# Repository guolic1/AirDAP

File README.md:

# AirDAP

基于 ESP32-S3 的无线调试器，支持 CMSIS-DAP 调试烧录和串口通信。
通过 USB 直连，或使用 Windows / Linux 主机服务将网络设备映射为 USB 调试器和串口。

支持蓝牙 / USB 配网、Wi-Fi 扫描、设备信息查看及 OTA 升级。

## 快速开始

从 [Releases](https://github.com/guolic1/AirDAP/releases/latest) 下载服务管理器和固件：

- **Windows**：双击服务管理器安装服务，可设置端口和开机自启。默认管理地址为 `http://airdap.localhost:8080`。
- **Linux**：按 [主机服务说明](host/README.md) 构建并安装 systemd 服务。
- **固件**：`app.bin` 用于 OTA；`full.bin` 用于首次烧录或恢复，写入地址为 `0x0`，会清除配网数据。

Windows 的 USB/IP 映射需安装 [usbip-win2 驱动和客户端](https://github.com/vadimgrn/usbip-win2/releases)。

## 项目目录

- [firmware/](firmware/README.md)：ESP-IDF 固件与构建说明。
- [host/](host/README.md)：Rust 主机服务、Web 管理页和服务安装工具。
- [circuit/](circuit/)：KiCad 原理图与 PCB。
- [docs/hardware-pinmap.md](docs/hardware-pinmap.md)：硬件引脚约定。

## 许可证

[MIT](LICENSE)。第三方依赖遵循各自的许可证。

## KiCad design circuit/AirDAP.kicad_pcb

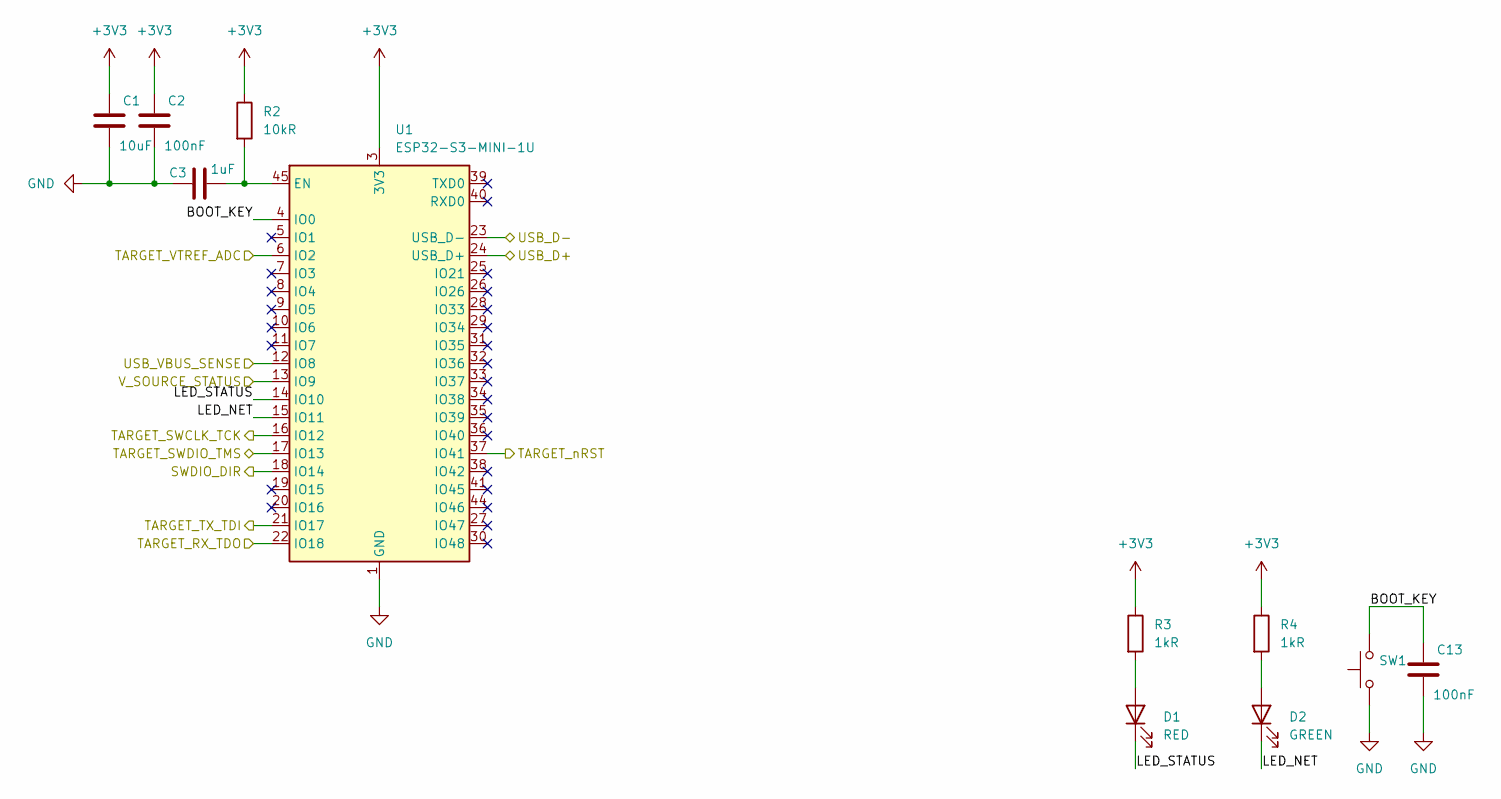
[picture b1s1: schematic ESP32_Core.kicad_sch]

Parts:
C1: 10uF; C_0402_1005Metric
C2, C13: 100nF; C_0402_1005Metric
C3: 1uF; C_0402_1005Metric
D1: RED; LED_0603_1608Metric
D2: GREEN; LED_0603_1608Metric
R2: 10kR; R_0402_1005Metric
R3, R4: 1kR; R_0402_1005Metric
SW1: SW_Push; SW_Push_SPST_NO_Alps_SKRK
U1: ESP32-S3-MINI-1U; ESP32-S2-MINI-1U

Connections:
+3V3: C1.1, C2.1, R2.1, R3.1, R4.1, U1.3 (3V3); also elsewhere on the board
/ESP32 Core/BOOT_KEY: C13.1, SW1.2, U1.4 (IO0)
/ESP32 Core/LED_NET: D2.1 (K), U1.15 (IO11)
/ESP32 Core/LED_STATUS: D1.1 (K), U1.14 (IO10)
/ESP32 Core/SWDIO_DIR: U1.18 (IO14); also elsewhere on the board
/ESP32 Core/TARGET_RX_TDO: U1.22 (IO18); also elsewhere on the board
/ESP32 Core/TARGET_SWCLK_TCK: U1.16 (IO12); also elsewhere on the board
/ESP32 Core/TARGET_SWDIO_TMS: U1.17 (IO13); also elsewhere on the board
/ESP32 Core/TARGET_TX_TDI: U1.21 (IO17); also elsewhere on the board
/ESP32 Core/TARGET_VTREF_ADC: U1.6 (IO2); also elsewhere on the board
/ESP32 Core/TARGET_nRST: U1.37 (IO41); also elsewhere on the board
/ESP32 Core/USB_D+: U1.24 (USB_D+); also elsewhere on the board
/ESP32 Core/USB_D-: U1.23 (USB_D-); also elsewhere on the board
/ESP32 Core/USB_VBUS_SENSE: U1.12 (IO8); also elsewhere on the board
/ESP32 Core/V_SOURCE_STATUS: U1.13 (IO9); also elsewhere on the board
GND: C1.2, C2.2, C3.1, C13.2, SW1.1, U1.1 (GND), U1.2 (GND), U1.42 (GND), U1.43 (GND), U1.46 (GND), U1.47 (GND), U1.48 (GND), U1.49 (GND), U1.50 (GND), U1.51 (GND), U1.52 (GND), U1.53 (GND), U1.54 (GND), U1.55 (GND), U1.56 (GND), U1.57 (GND), U1.58 (GND), U1.59 (GND), U1.60 (GND), U1.61 (GND), U1.62 (GND), U1.63 (GND), U1.64 (GND), U1.65 (GND); also elsewhere on the board
unnamed: D1.2 (A), R3.2
unnamed: D2.2 (A), R4.2
unnamed: C3.2, R2.2, U1.45 (EN)

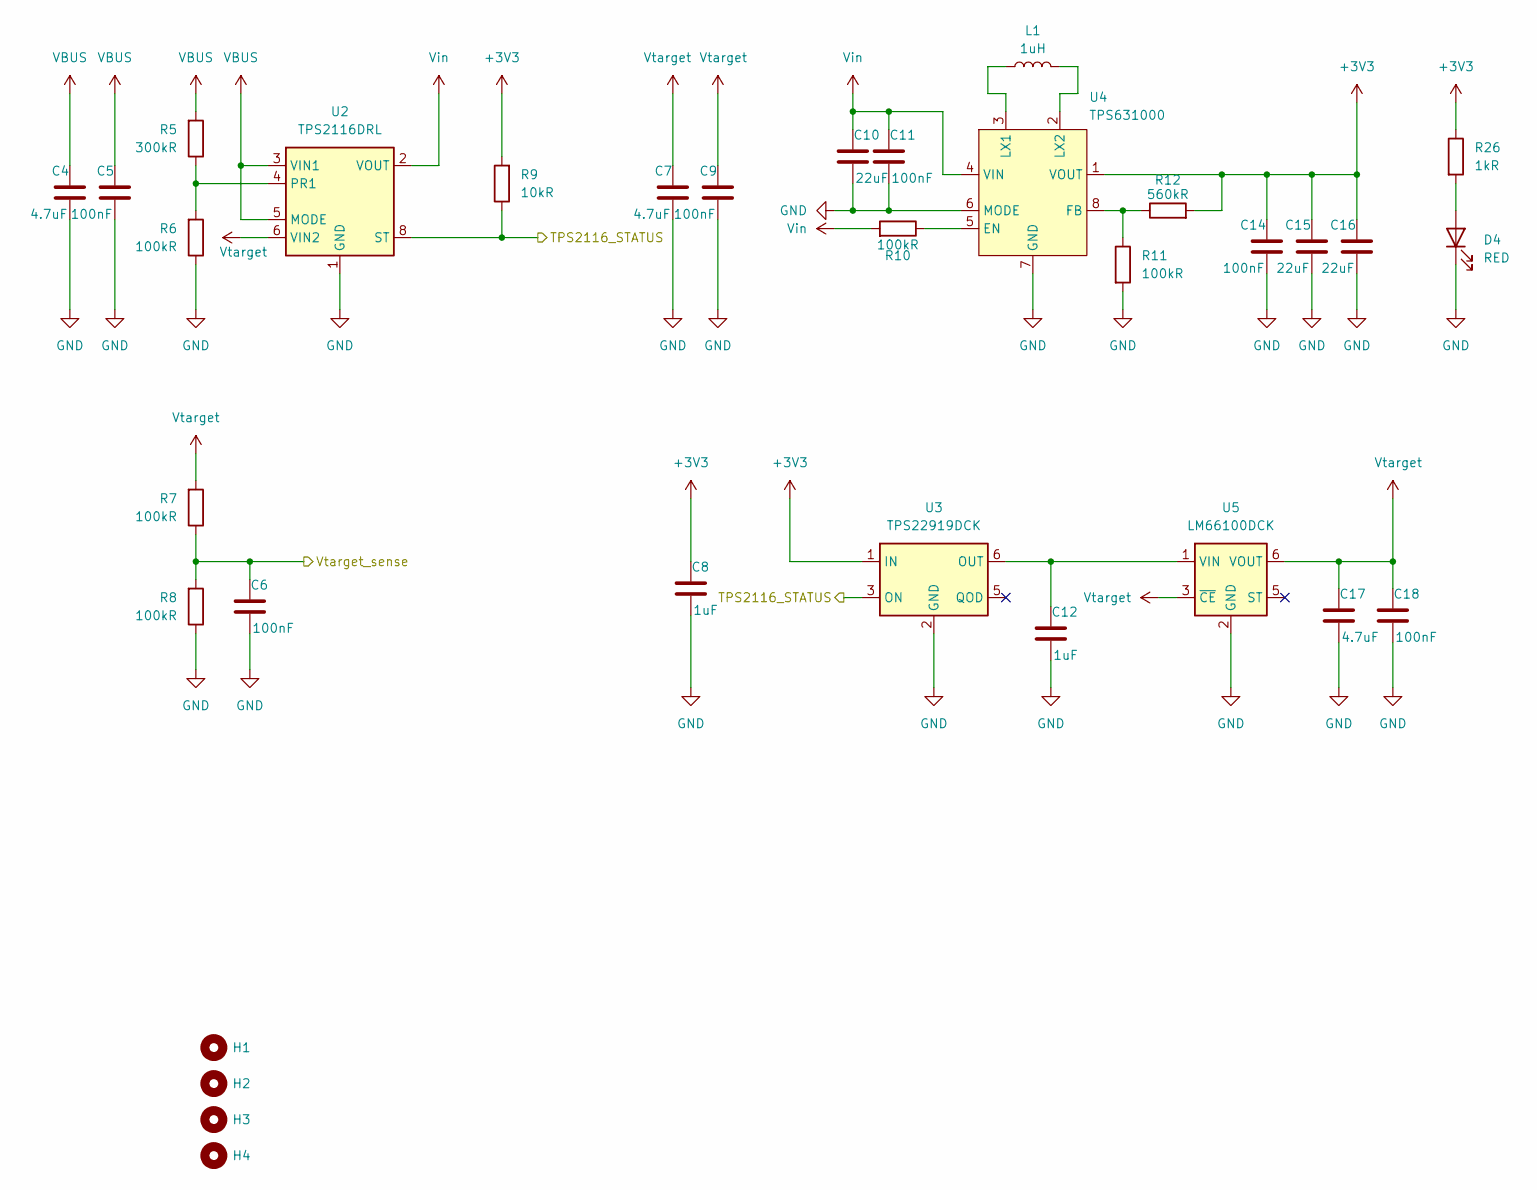
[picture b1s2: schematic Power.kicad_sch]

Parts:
C4, C7, C17: 4.7uF; C_0402_1005Metric
C5, C6, C9, C11, C14, C18: 100nF; C_0402_1005Metric
C8, C12: 1uF; C_0402_1005Metric
C10, C15, C16: 22uF; C_0603_1608Metric
D4: RED; LED_0603_1608Metric
H1, H2, H3, H4: MountingHole; MountingHole_2.2mm_M2
L1: 1uH; L_1008_2520Metric
R5: 300kR; R_0402_1005Metric
R6, R7, R8, R10, R11: 100kR; R_0402_1005Metric
R9: 10kR; R_0402_1005Metric
R12: 560kR; R_0402_1005Metric
R26: 1kR; R_0402_1005Metric
U2: TPS2116DRL; SOT-583-8
U3: TPS22919DCK; SOT-363_SC-70-6
U4: TPS631000; SOT-583-8
U5: LM66100DCK; SOT-363_SC-70-6

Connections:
+3V3: C8.1, C14.1, C15.1, C16.1, R9.2, R12.2, R26.1, U3.1 (IN), U4.1 (VOUT); also elsewhere on the board
/ESP32 Core/TARGET_VTREF_ADC: C6.1, R7.1, R8.2; also elsewhere on the board
/ESP32 Core/V_SOURCE_STATUS: R9.1, U2.8 (ST), U3.3 (ON); also elsewhere on the board
GND: C4.2, C5.2, C6.2, C7.2, C8.2, C9.2, C10.2, C11.2, C12.2, C14.2, C15.2, C16.2, C17.2, C18.2, D4.1 (K), R6.1, R8.1, R11.2, U2.1 (GND), U3.2 (GND), U4.6 (MODE), U4.7 (GND), U5.2 (GND); also elsewhere on the board
unnamed: D4.2 (A), R26.2
unnamed: R5.1, R6.2, U2.4 (PR1)
unnamed: C12.1, U3.6 (OUT), U5.1 (VIN)
unnamed: R10.1, U4.5 (EN)
unnamed: R11.1, R12.1, U4.8 (FB)
unnamed: L1.1, U4.3 (LX1)
unnamed: L1.2, U4.2 (LX2)
VBUS: C4.1, C5.1, R5.2, U2.3 (VIN1), U2.5 (MODE); also elsewhere on the board
Vin: C10.1, C11.1, R10.2, U2.2 (VOUT), U2.7 (VOUT), U4.4 (VIN)
Vtarget: C7.1, C9.1, C17.1, C18.1, R7.2, U2.6 (VIN2), U5.3 (~CE), U5.6 (VOUT); also elsewhere on the board

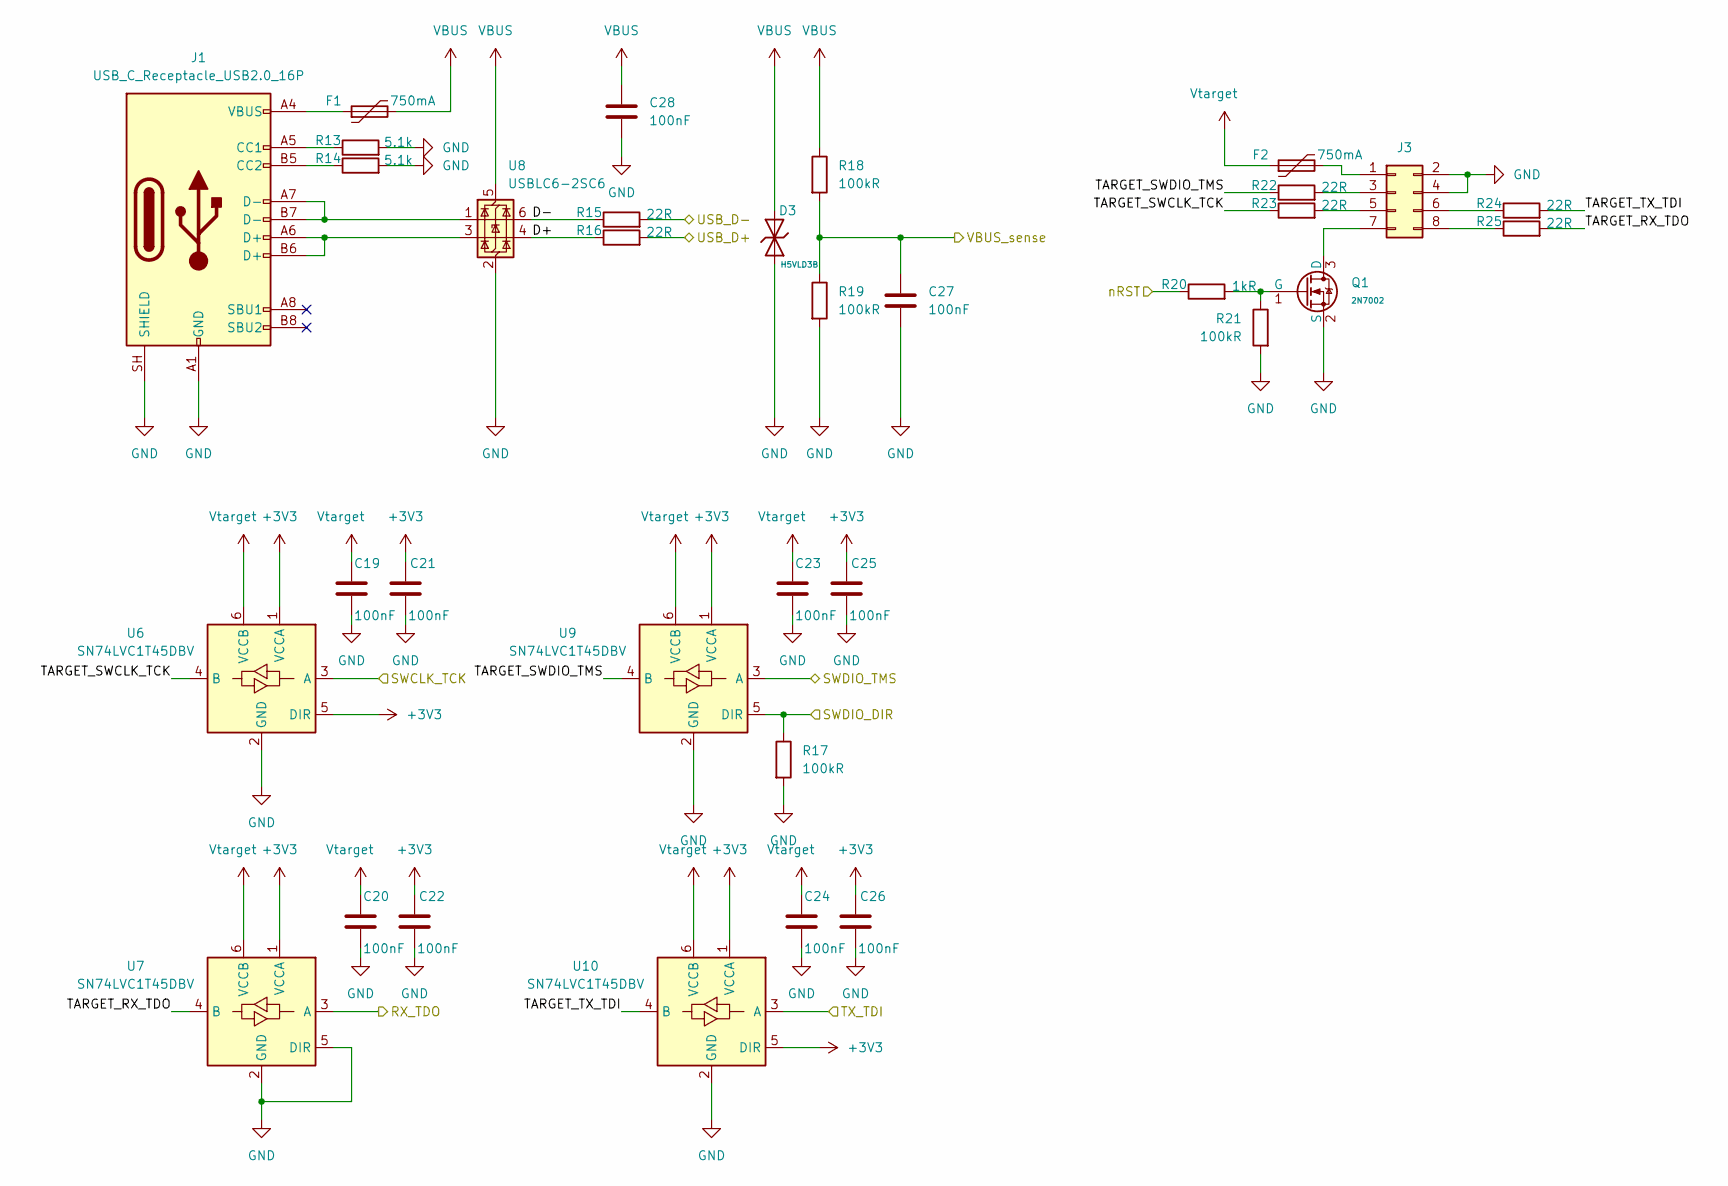
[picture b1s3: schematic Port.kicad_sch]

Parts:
C19, C20, C21, C22, C23, C24, C25, C26, C27, C28: 100nF; C_0402_1005Metric
D3: H5VLD3B; D_SOD-323; Part H5VLD3B; LCSC C20615805
F1, F2: 750mA; Fuse_0805_2012Metric
J1: USB_C_Receptacle_USB2.0_16P; USB_C_Receptacle_Palconn_UTC16-G
J3: Conn_02x04_Odd_Even; PinHeader_2x04_P2.54mm_Vertical
Q1: 2N7002; SOT-323_SC-70; Part 2N7002; LCSC C8545
R13, R14: 5.1k; R_0402_1005Metric
R15, R16, R22, R23, R24, R25: 22R; R_0402_1005Metric
R17, R18, R19, R21: 100kR; R_0402_1005Metric
R20: 1kR; R_0402_1005Metric
U6, U7, U9, U10: SN74LVC1T45DBV; SOT-23-6
U8: USBLC6-2SC6; SOT-23-6

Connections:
+3V3: C21.1, C22.1, C25.1, C26.1, U6.1 (VCCA), U6.5 (DIR), U7.1 (VCCA), U9.1 (VCCA), U10.1 (VCCA), U10.5 (DIR); also elsewhere on the board
/ESP32 Core/SWDIO_DIR: R17.1, U9.5 (DIR); also elsewhere on the board
/ESP32 Core/TARGET_RX_TDO: U7.3 (A); also elsewhere on the board
/ESP32 Core/TARGET_SWCLK_TCK: U6.3 (A); also elsewhere on the board
/ESP32 Core/TARGET_SWDIO_TMS: U9.3 (A); also elsewhere on the board
/ESP32 Core/TARGET_TX_TDI: U10.3 (A); also elsewhere on the board
/ESP32 Core/TARGET_nRST: R20.1; also elsewhere on the board
/ESP32 Core/USB_D+: R16.2; also elsewhere on the board
/ESP32 Core/USB_D-: R15.2; also elsewhere on the board
/ESP32 Core/USB_VBUS_SENSE: C27.1, R18.2, R19.1; also elsewhere on the board
/Port/D+: R16.1, U8.4 (I/O2)
/Port/D-: R15.1, U8.6 (I/O1)
/Port/TARGET_RX_TDO: R25.2, U7.4 (B)
/Port/TARGET_SWCLK_TCK: R23.1, U6.4 (B)
/Port/TARGET_SWDIO_TMS: R22.1, U9.4 (B)
/Port/TARGET_TX_TDI: R24.2, U10.4 (B)
GND: C19.2, C20.2, C21.2, C22.2, C23.2, C24.2, C25.2, C26.2, C27.2, C28.2, D3.1, J1.A1 (GND), J1.A12 (GND), J1.B1 (GND), J1.B12 (GND), J1.SH (SHIELD), J3.2, J3.4, Q1.2 (S), R13.2, R14.2, R17.2, R19.2, R21.2, U6.2 (GND), U7.2 (GND), U7.5 (DIR), U8.2 (GND), U9.2 (GND), U10.2 (GND); also elsewhere on the board
unnamed: F1.1, J1.A4 (VBUS), J1.A9 (VBUS), J1.B4 (VBUS), J1.B9 (VBUS)
unnamed: J1.A5 (CC1), R13.1
unnamed: J1.B5 (CC2), R14.1
unnamed: J1.A6 (D+), J1.B6 (D+), U8.3 (I/O2)
unnamed: J1.A7 (D-), J1.B7 (D-), U8.1 (I/O1)
unnamed: F2.2, J3.1
unnamed: J3.3, R22.2
unnamed: J3.5, R23.2
unnamed: J3.6, R24.1
unnamed: J3.7, Q1.3 (D)
unnamed: J3.8, R25.1
unnamed: Q1.1 (G), R20.2, R21.1
VBUS: C28.1, D3.2, F1.2, R18.1, U8.5 (VBUS); also elsewhere on the board
Vtarget: C19.1, C20.1, C23.1, C24.1, F2.1, U6.6 (VCCB), U7.6 (VCCB), U9.6 (VCCB), U10.6 (VCCB); also elsewhere on the board

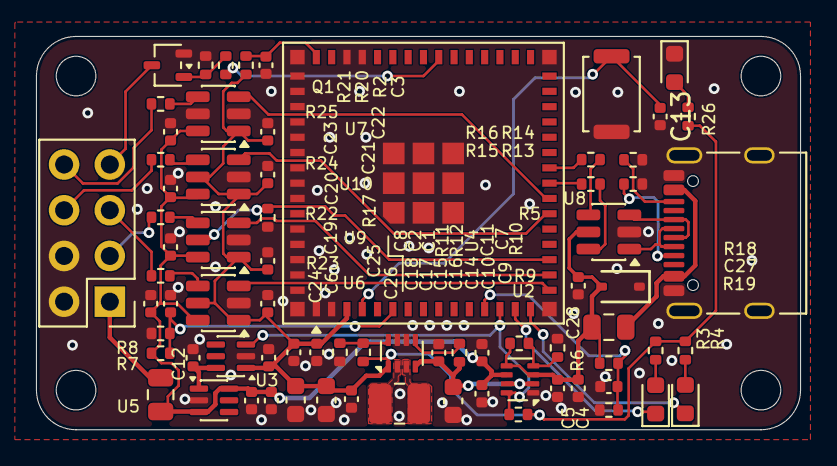
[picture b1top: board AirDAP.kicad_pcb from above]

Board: 2 copper layers, 42.5 x 21.8 mm, 78 parts (0 on the bottom side), 47 nets.
